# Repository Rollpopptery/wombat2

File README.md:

# Wombat II

## Repository layout

- `circuit/` — KiCad schematic and PCB design
- `software/` — all software

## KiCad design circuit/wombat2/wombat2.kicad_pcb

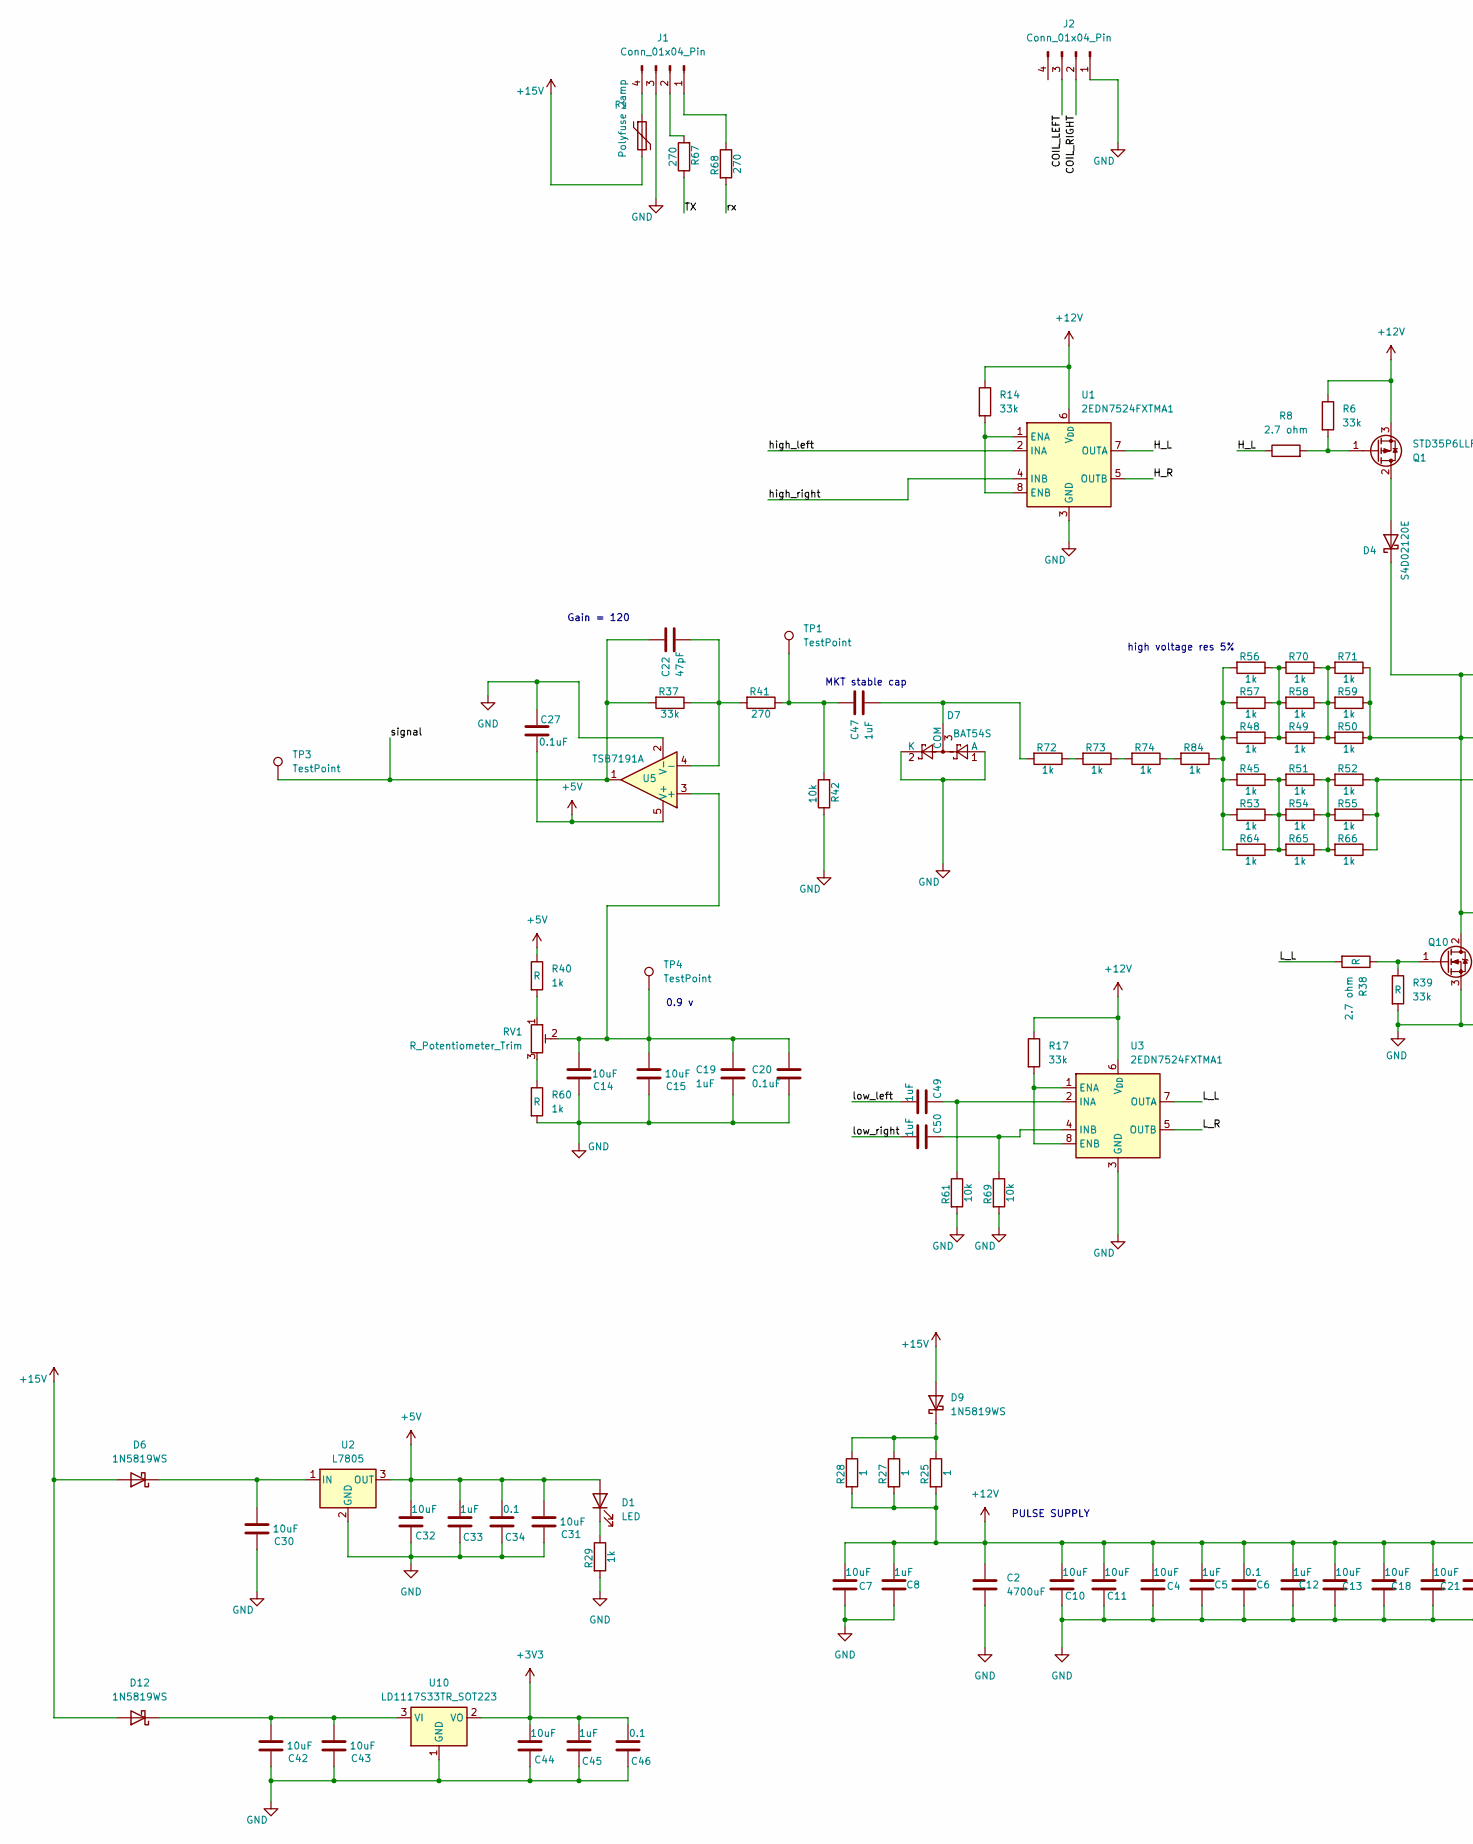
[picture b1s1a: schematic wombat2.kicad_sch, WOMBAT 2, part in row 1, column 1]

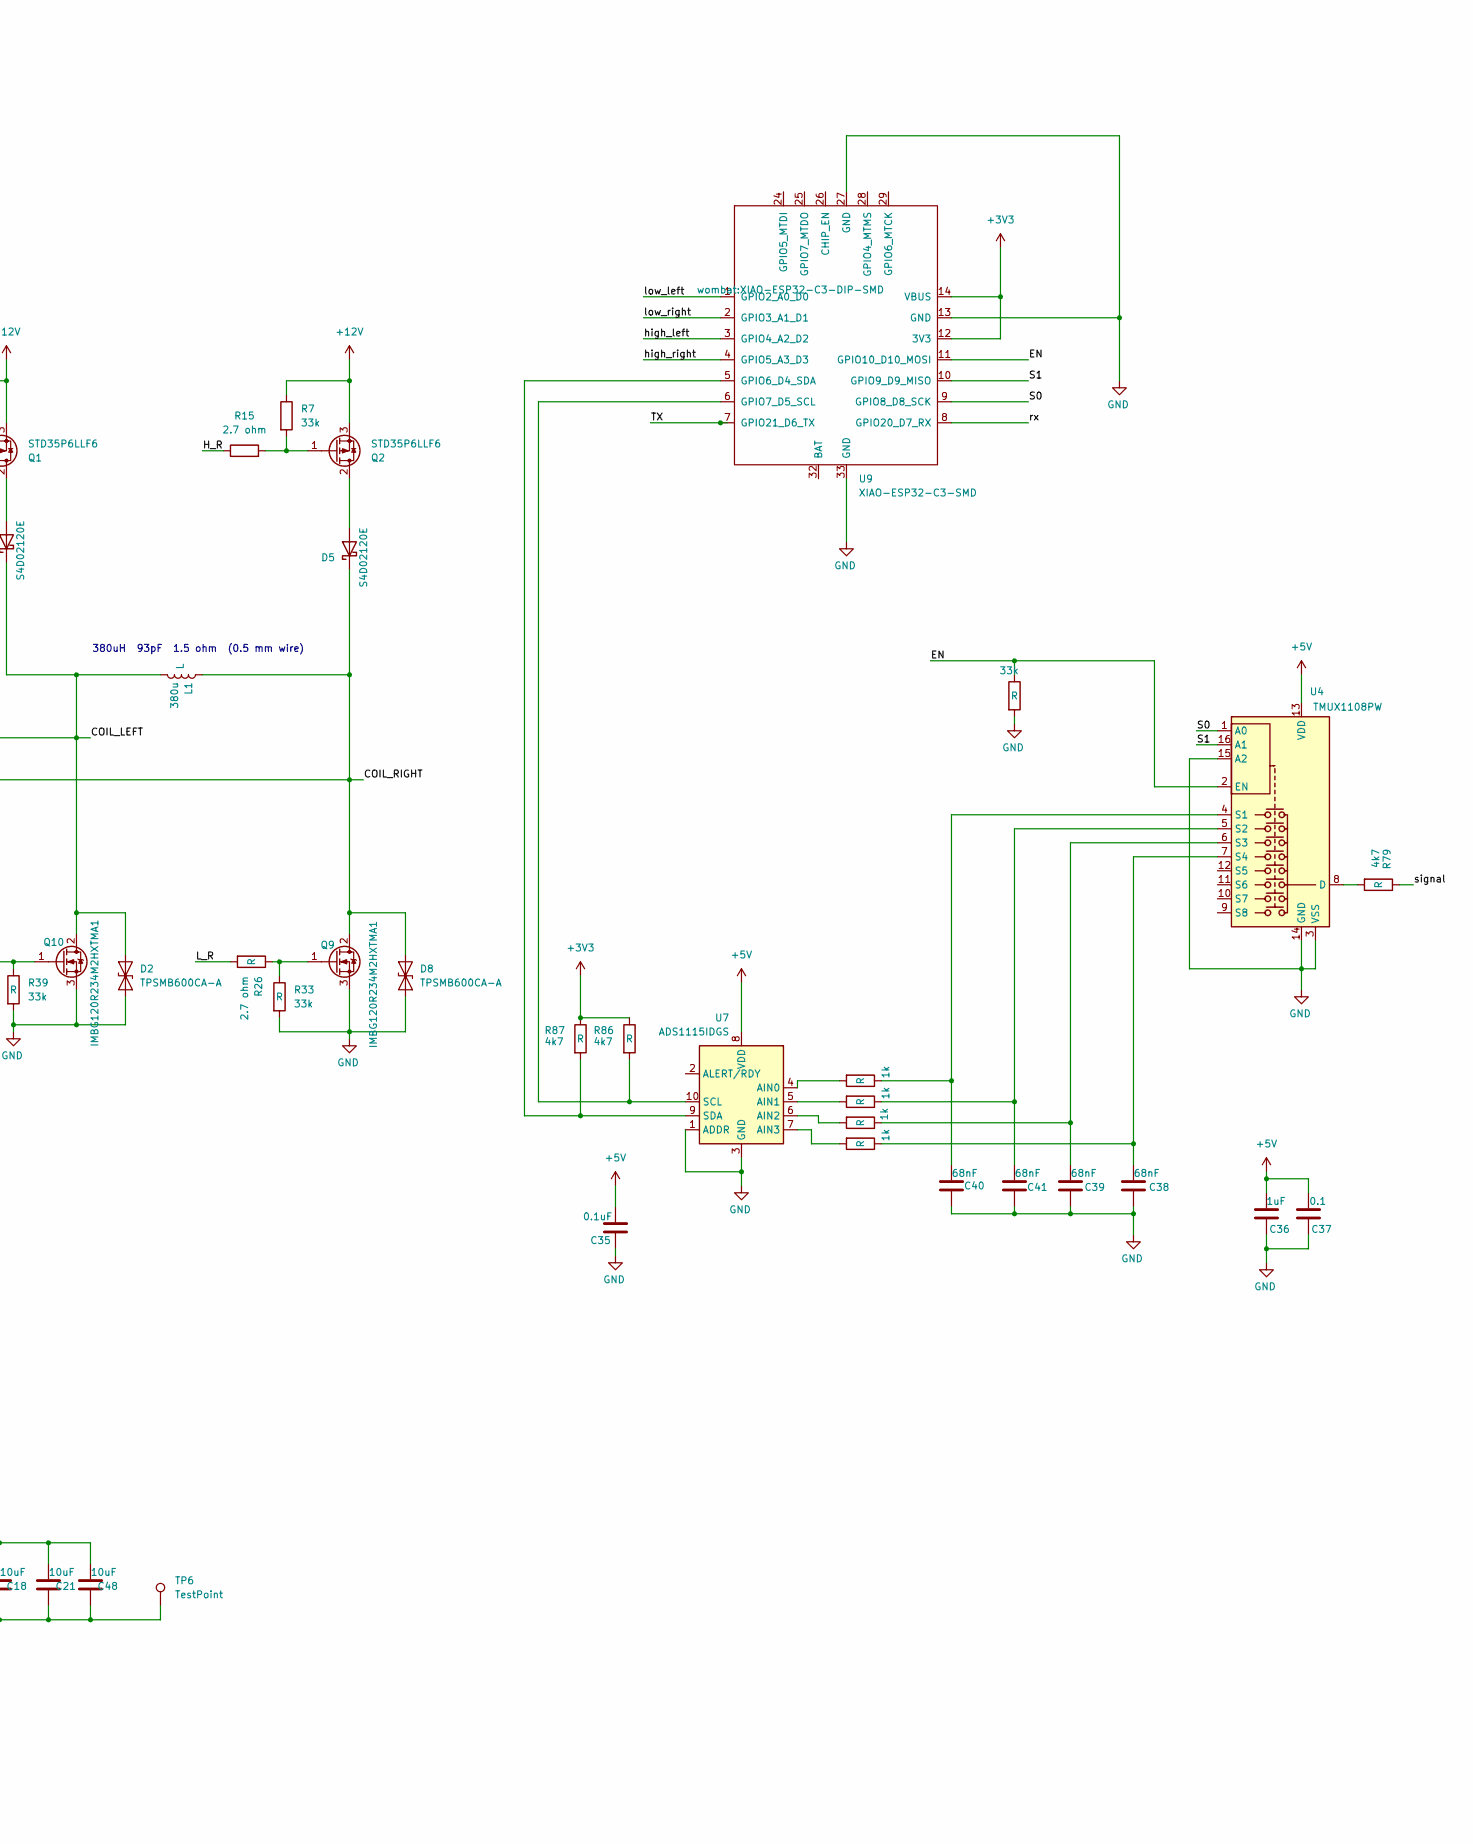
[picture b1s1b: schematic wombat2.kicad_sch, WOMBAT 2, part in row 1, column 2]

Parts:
C2: 4700uF; C_Radial_D16.0mm_H25.0mm_P7.50mm
C4, C7, C10, C11, C13, C15, C18, C21, C30, C31, C32, C42, C43, C44, C48: 10uF; C_1206_3216Metric_Pad1.33x1.80mm_HandSolder
C5, C8, C12, C19, C33, C36, C45, C49, C50: 1uF; C_0805_2012Metric
C6, C34, C37, C46: 0.1; C_0805_2012Metric
C14: 10uF; C_1206_3216Metric
C20, C27: 0.1uF; LED_0805_2012Metric
C22: 47pF; LED_0805_2012Metric
C35: 0.1uF
C38, C39, C40, C41: 68nF; C_Rect_L9.0mm_W5.1mm_P7.50mm_MKT
C47: 1uF; C_Rect_L10.3mm_W5.0mm_P7.50mm_MKS4
D1: LED; LED_0805_2012Metric_Pad1.15x1.40mm_HandSolder
D2, D8: TPSMB600CA-A; D_SMA
D4, D5: S4D02120E; TO-252-2_TabPin1
D6, D9, D12: 1N5819WS; D_SMA
D7: BAT54S; SOT-23
F1: Polyfuse 2amp; C_1210_3225Metric
J1, J2: Conn_01x04_Pin; PhoenixContact_GMSTBVA_2,5_4-G_1x04_P7.50mm_Vertical
L1: 380u; PhoenixContact_GMSTBA_2,5_2-G-7,62_1x02_P7.62mm_Horizontal
Q1, Q2: STD35P6LLF6; TO-263-2
Q9, Q10: IMBG120R234M2HXTMA1; TO-263-7_TabPin4
R6, R7, R33, R37, R39, R85: 33k; R_0805_2012Metric
R8, R15, R26, R38: 2.7 ohm; R_0805_2012Metric
R14, R17: 33k; C_0805_2012Metric
R25, R27, R28: 1; R_2512_6332Metric
R29: 1k; LED_0805_2012Metric
R40, R45, R48, R49, R50, R51, R52, R53, R54, R55, R56, R57, R58, R59, R60, R64, R65, R66, R70, R71, R72, R73, R74, R80, R81, R82, R83, R84: 1k; R_0805_2012Metric
R41: 270; R_0805_2012Metric
R42, R61, R69: 10k; R_0805_2012Metric
R67, R68: 270; C_0805_2012Metric
R79, R86, R87: 4k7; R_0805_2012Metric
RV1: R_Potentiometer_Trim; Potentiometer_Bourns_3266Y_Vertical
TP1, TP3, TP4, TP6: TestPoint; TestPoint_Pad_2.0x2.0mm
U1, U3: 2EDN7524FXTMA1; SOIC-8_3.9x4.9mm_P1.27mm
U2: L7805; TO-252-2
U4: TMUX1108PW; TSSOP-16_4.4x5mm_P0.65mm
U5: TSB7191A; SOT-23-5
U7: ADS1115IDGS; TSSOP-10_3x3mm_P0.5mm
U9: XIAO-ESP32-C3-SMD; XIAO-ESP32-C3-DIP-SMD
U10: LD1117S33TR_SOT223; SOT-223-3_TabPin2

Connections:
+3V3: C44.2, C45.2, C46.2, R86.1, R87.1, U9.12 (3V3), U9.14 (VBUS), U10.2 (VO)
+5V: C27.2, C31.2, C32.2, C33.2, C34.2, C35.2, C36.2, C37.2, D1.2 (A), R40.1, U2.3 (OUT), U4.13 (VDD), U5.5 (V+), U7.8 (VDD)
+12V: C2.1, C4.2, C5.2, C6.2, C7.2, C8.2, C10.2, C11.2, C12.2, C13.2, C18.2, C21.2, C48.2, Q1.3 (S), Q2.3 (S), R6.1, R7.1, R14.1, R17.1, R25.2, R27.2, R28.2, U1.6 (V_{DD}), U3.6 (V_{DD})
+15V: D6.2 (A), D9.2 (A), D12.2 (A), F1.2
/COIL_LEFT: D2.2 (A2), D4.1 (K), J2.3, L1.2, Q10.2 (D), R50.1, R59.1, R71.1
/COIL_RIGHT: D5.1 (K), D8.2 (A2), J2.2, L1.1, Q9.2 (D), R52.1, R55.1, R66.1
/EN: R85.1, U4.2 (EN), U9.11 (GPIO10_D10_MOSI)
/H_L: R8.1, U1.7 (OUTA)
/H_R: R15.1, U1.5 (OUTB)
/L_L: R38.2, U3.7 (OUTA)
/L_R: R26.2, U3.5 (OUTB)
/S0: U4.1 (A0), U9.9 (GPIO8_D8_SCK)
/S1: U4.16 (A1), U9.10 (GPIO9_D9_MISO)
/TX: R67.1, U9.7 (GPIO21_D6_TX)
/high_left: U1.2 (INA), U9.3 (GPIO4_A2_D2)
/high_right: U1.4 (INB), U9.4 (GPIO5_A3_D3)
/low_left: C49.2, U9.1 (GPIO2_A0_D0)
/low_right: C50.2, U9.2 (GPIO3_A1_D1)
/rx: R68.2, U9.8 (GPIO20_D7_RX)
/signal: C22.1, R37.2, R79.1, TP3.1 (1_1), U5.1
GND: C2.2, C4.1, C5.1, C6.1, C7.1, C8.1, C10.1, C11.1, C12.1, C13.1, C14.1, C15.1, C18.1, C19.2, C20.2, C21.1, C27.1, C30.1, C31.1, C32.1, C33.1, C34.1, C35.1, C36.1, C37.1, C38.1, C39.1, C40.1, C41.1, C42.1, C43.1, C44.1, C45.1, C46.1, C48.1, D2.1 (A1), D7.1 (A), D7.2 (K), D8.1 (A1), J1.3, J2.1, Q9.3 (S), Q10.3 (S), R29.2, R33.2, R39.2, R42.1, R60.2, R61.2, R69.2, R85.2, TP6.1 (1_1), U1.3 (GND), U2.2 (GND), U3.3 (GND), U4.3 (VSS), U4.14 (GND), U4.15 (A2), U5.2 (V-), U7.1 (ADDR), U7.3 (GND), U9.13 (GND), U9.27 (GND), U9.33 (GND), U10.1 (GND)
unnamed: C47.1, R41.1, R42.2, TP1.1 (1_1)
unnamed: D1.1 (K), R29.1
unnamed: D4.2 (A), Q1.2 (D)
unnamed: D5.2 (A), Q2.2 (D)
unnamed: C30.2, D6.1 (K), U2.1 (IN)
unnamed: C47.2, D7.3 (COM), R72.2
unnamed: D9.1 (K), R25.1, R27.1, R28.1
unnamed: C42.2, C43.2, D12.1 (K), U10.3 (VI)
unnamed: J1.1, R68.1
unnamed: J1.2, R67.2
unnamed: F1.1, J1.4
unnamed: Q1.1 (G), R6.2, R8.2
unnamed: Q2.1 (G), R7.2, R15.2
unnamed: Q9.1 (G), R26.1, R33.1
unnamed: Q10.1 (G), R38.1, R39.1
unnamed: R40.2, RV1.1
unnamed: R45.1, R51.2, R53.1, R54.2, R64.1, R65.2
unnamed: R45.2, R48.2, R53.2, R56.2, R57.2, R64.2, R84.1
unnamed: R48.1, R49.2, R56.1, R57.1, R58.2, R70.2
unnamed: R49.1, R50.2, R58.1, R59.2, R70.1, R71.2
unnamed: R51.1, R52.2, R54.1, R55.2, R65.1, R66.2
unnamed: R60.1, RV1.3
unnamed: R72.1, R73.2
unnamed: R73.1, R74.2
unnamed: R74.1, R84.2
unnamed: R14.2, U1.1 (ENA), U1.8 (ENB)
unnamed: R17.2, U3.1 (ENA), U3.8 (ENB)
unnamed: C49.1, R61.1, U3.2 (INA)
unnamed: C50.1, R69.1, U3.4 (INB)
unnamed: R79.2, U4.8 (D)
unnamed: C40.2, R80.1, U4.4 (S1)
unnamed: C41.2, R81.1, U4.5 (S2)
unnamed: C39.2, R82.1, U4.6 (S3)
unnamed: C38.2, R83.1, U4.7 (S4)
unnamed: C14.2, C15.2, C19.1, C20.1, RV1.2, TP4.1 (1_1), U5.3 (+)
unnamed: C22.2, R37.1, R41.2, U5.4 (-)
unnamed: R80.2, U7.4 (AIN0)
unnamed: R81.2, U7.5 (AIN1)
unnamed: R82.2, U7.6 (AIN2)
unnamed: R83.2, U7.7 (AIN3)
unnamed: R86.2, U7.10 (SCL), U9.6 (GPIO7_D5_SCL)
unnamed: R87.2, U7.9 (SDA), U9.5 (GPIO6_D4_SDA)

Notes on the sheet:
PULSE SUPPLY
Gain = 120
MKT stable cap
380uH 93pF 1.5 ohm (0.5 mm wire)
0.9 v
high voltage res 5%

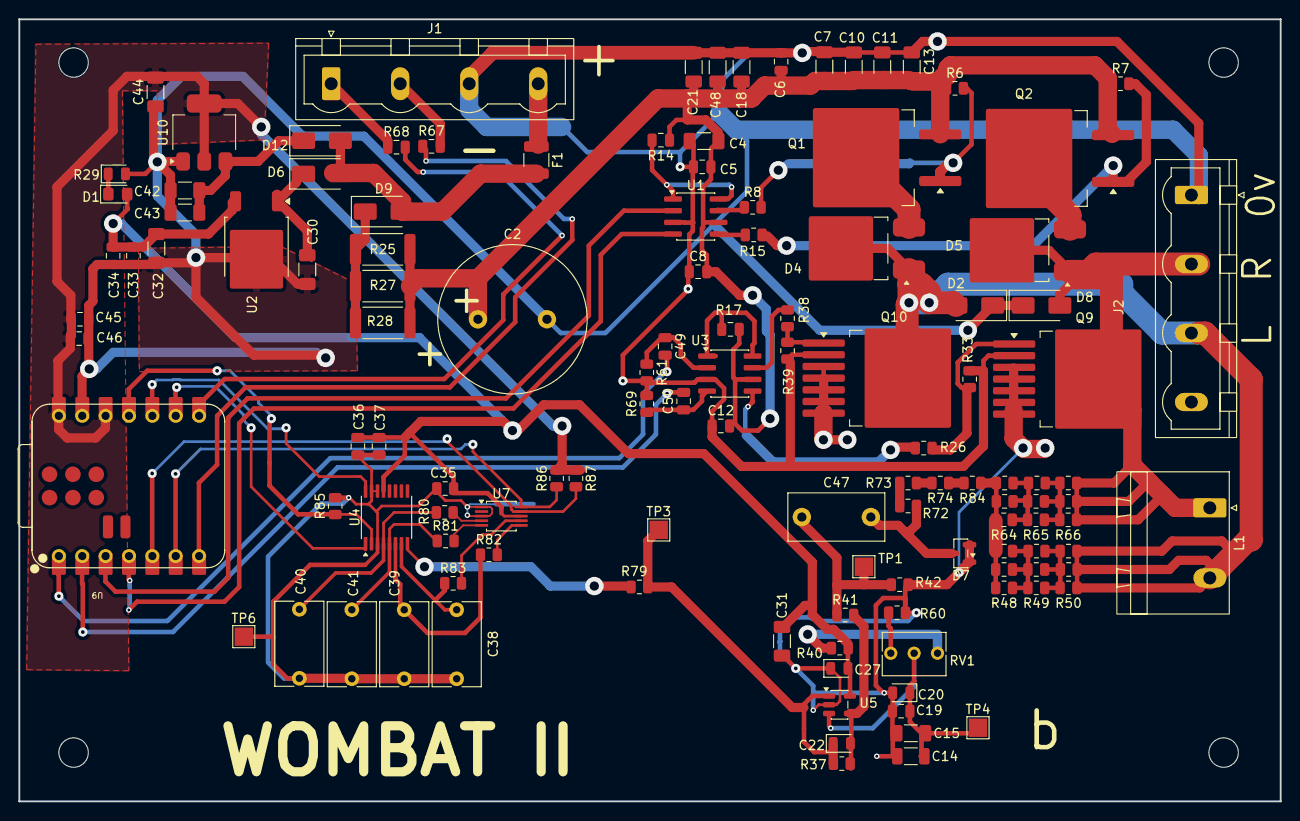
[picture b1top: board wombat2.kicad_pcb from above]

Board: 2 copper layers, 137.1 x 85.0 mm, 122 parts (0 on the bottom side), 63 nets.

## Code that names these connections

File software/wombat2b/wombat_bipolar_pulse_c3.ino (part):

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// GPIO2 is a strapping pin (must be HIGH at boot): the low-left FET is likely
// ON from power-up until setup() runs. High-side gates (active-LOW) need
// external pull-ups so they stay OFF while the C3 is in reset.
#define PIN_HIGH_LEFT   4   // A2/D2  high-side LEFT  (CCW)
#define PIN_HIGH_RIGHT  5   // A3/D3  high-side RIGHT (CW)
#define PIN_LOW_LEFT    2   // A0/D0  low-side  LEFT
#define PIN_LOW_RIGHT   3   // A1/D1  low-side  RIGHT
#define PIN_DEBUG       20  // D7     scope this (UART RX, unused - serial is USB-CDC)

// TMUX1108 8:1 sample MUX, VDD = 5 V -> 4 hold caps on channels S1..S4.
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#define GPIO_CLR(p)  REG_WRITE(GPIO_OUT_W1TC_REG, 1UL << (p))

// High-side ACTIVE-LOW, low-side ACTIVE-HIGH.
#define HIGH_LEFT_ON    GPIO_CLR(PIN_HIGH_LEFT)
#define HIGH_LEFT_OFF   GPIO_SET(PIN_HIGH_LEFT)
#define HIGH_RIGHT_ON   GPIO_CLR(PIN_HIGH_RIGHT)
#define HIGH_RIGHT_OFF  GPIO_SET(PIN_HIGH_RIGHT)
#define LOW_LEFT_ON     GPIO_SET(PIN_LOW_LEFT)
#define LOW_LEFT_OFF    GPIO_CLR(PIN_LOW_LEFT)
#define LOW_RIGHT_ON    GPIO_SET(PIN_LOW_RIGHT)
#define LOW_RIGHT_OFF   GPIO_CLR(PIN_LOW_RIGHT)
#define D2_HIGH         GPIO_SET(PIN_DEBUG)
#define D2_LOW          GPIO_CLR(PIN_DEBUG)

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// ---- BENCH TEST MODE: simple unipolar pulse, NO active damping ---------------
// 1 = fire HIGH_LEFT + LOW_RIGHT on EVERY pulse (single direction, no bipolar
//     alternation). At pulse end the bridge just opens; the coil rings down
//     through the passive damping resistor only. LOW_LEFT is never asserted, so
//     there is NO active damping pulse. g_damp_delay_cyc / g_damp_seg_cyc and
//     the '+ - [ ]' serial keys are inert in this mode.
// 0 = full bipolar engine with mirrored active damping (the intended design).
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  HIGH_LEFT_OFF;  HIGH_RIGHT_OFF;  LOW_LEFT_OFF;  LOW_RIGHT_OFF;  D2_LOW;
  MUX_DISCONNECT;  MUX_ADDR(0);

  pinMode(PIN_HIGH_LEFT,  OUTPUT);
  pinMode(PIN_HIGH_RIGHT, OUTPUT);
  pinMode(PIN_LOW_LEFT,   OUTPUT);
  pinMode(PIN_LOW_RIGHT,  OUTPUT);
  pinMode(PIN_DEBUG,      OUTPUT);
  pinMode(PIN_MUX_A0,     OUTPUT);
  pinMode(PIN_MUX_A1,     OUTPUT);
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

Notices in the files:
software/wombat2b/wombat_bipolar_pulse_c3.ino:
arduino-esp32 core 3.x (a core-2.x timer block is included). MIT (see LICENSE).
